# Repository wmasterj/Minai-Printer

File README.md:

# Minai Printer

A very cheap Wi-Fi receipt printer built for AI agents to print to.

The device is deliberately dumb: it receives a 384-pixel-wide black-and-white
image over Wi-Fi or USB and prints it on 58 mm thermal paper. Layout, fonts and
intelligence live in software upstream.

- Target build cost: about $26 per unit for the first 100, about $12 at 1,000 (estimates)
- Power: any USB-C charger, no battery
- Interface: one button, one light

## Documents

- [Hardware specification](docs/hardware-spec.md) — requirements, reference
  architecture, cost estimate, build plan, and what to ask a manufacturer for.

- [Reference design](hardware/README.md) — schematic, routed board, gerbers
  and parts list with links for the main circuit board.

- [Enclosure](hardware/enclosure/README.md) — 3D model of the case, with
  STEP and STL files for the four printed parts.

## Status

Specification and a first-pass reference board design, checked in software
only, plus a concept enclosure. Nothing has been built. No firmware yet.

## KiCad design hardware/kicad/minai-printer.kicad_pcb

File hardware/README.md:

# Minai Printer — main board reference design (rev 0.1)

A complete first-pass design of the printer's one circuit board: schematic,
routed 2-layer board, manufacturing files and parts list.

**Status: designed and rule-checked in software only. Nothing has been built
or powered. Treat it as a starting point for an electronics engineer or
supplier to review, not as files to order 100 boards from.** The list of
things that must be checked first is in [Before ordering](#before-ordering).

| Top copper and silkscreen | Bottom copper |
|---|---|
|  |  |

## What is here

| Path | What it is |
|---|---|
| `kicad/minai-printer.kicad_pro` | KiCad 9 project. Open this to view or edit the schematic and board |
| `outputs/schematic.pdf` | Schematic, one A3 page |
| `outputs/board-top.pdf`, `board-bottom.pdf` | Board layers as PDF |
| `outputs/gerbers.zip` | Gerber and drill files for a PCB fabricator |
| `outputs/pick-and-place.csv` | Part positions for an assembly house |
| `outputs/bom.csv`, [`outputs/bom.md`](outputs/bom.md) | Parts list with search links for every line |
| `outputs/erc-report.txt`, `drc-report.txt` | KiCad rule-check reports |
| `gen/design.py` | The design itself: every part, pin, net and position, in one file |
| `gen/build.sh` | Regenerates everything above from `design.py` |

## The board at a glance

| Item | Value |
|---|---|
| Size | 62 × 49 mm, 2 layers, 1.6 mm, four M2 mounting holes |
| Parts | 53 placed parts, 31 BOM lines, all on the top side |
| Power in | USB-C, 5 V |
| Brain | ESP32-C3-WROOM-02 module (Wi-Fi, Bluetooth LE, native USB) |
| Print head drive | Direct from the module: data, clock, latch, two strobe groups |
| Head power | 5 V through a soft-started MOSFET switch, 2 × 1000 µF reservoir |
| Paper feed | DRV8833 dual H-bridge, 1 A current limit per coil |
| Sensing | Head thermistor, paper-out sensor, head-rail voltage |
| User interface | One button (also the firmware-flash button), one RGB LED |
| Mechanism connector | 30-pin, 1.0 mm pitch FPC |

### Pin map (ESP32-C3)

| GPIO | Signal | Notes |
|---|---|---|
| 0 | TM_ADC | Head thermistor, 30 kΩ divider |
| 1 | PS_ADC | Paper sensor phototransistor |
| 2 | HEAD_LAT | Latch, idle high (also satisfies the boot strap) |
| 3 | VH_SENSE | Head rail ÷ 2.47 |
| 4 | HEAD_CLK | Shift clock |
| 5 | VH_EN | High = head power and motor driver on. Pulled low |
| 6 | HEAD_DI | Shift data |
| 7 | HEAD_STB_A | Strobes 1–3. Pulled low |
| 8 | LED_DIN | RGB LED data, pulled high (boot strap) |
| 9 | BTN | Button to ground, pulled high (boot strap) |
| 10 | HEAD_STB_B | Strobes 4–6. Pulled low |
| 18 / 19 | USB D− / D+ | Flashing and USB serial |
| 20 / 21 | MOT_PH_A / MOT_PH_B | Motor phases; an inverter makes the complements |

All 13 usable pins are taken. That is why the motor uses two pins plus a
dual inverter instead of four pins.

## What was checked, and how

- **Schematic rule check (ERC): 0 errors.** 2 warnings, both about library
  bookkeeping (a custom symbol for the mechanism connector), not the circuit.
- **Board rule check (DRC): 0 errors, 0 unconnected nets, 0 shorts.** 31
  warnings, all silkscreen text overlapping pads or other text (cosmetic).
- **Schematic and board agree:** KiCad's parity check reports 0 differences,
  and both files are generated from the same netlist in `design.py`.

Not checked by anything: whether the circuit actually works, whether the
mechanism pinout is right, thermal behaviour, radio performance, EMC.

## Before ordering

These are known gaps, most important first.

1. **Mechanism pinout is not confirmed.** Connector J2 follows the Fujitsu
   FTP-628MCL101 layout. I could not open the datasheet from this session;
   pins 1–20, 23–24 and 27–30 match fragments of it found by web search;
   pins 21, 22 (ground) and 25, 26 (head power) are from memory. The
   compatible mechanism you actually buy (PT486F or similar) must be checked
   pin by pin against its own datasheet.
2. **Strobe polarity is assumed active-high.** R7 and R8 pull the strobes low
   so the head is off during reset. If the head is active-low, those two
   resistors must go to 3.3 V instead, or the head will burn at power-up.
3. **Motor coil pairing is assumed** to be pins 27–28 and 29–30. If the coils
   are paired differently the motor will not turn; this needs a board change,
   not firmware.
4. **FPC connector.** Fujitsu specifies Molex 52610-3071. The board uses the
   footprint for Molex 200528-0300 (same pitch and pin count) because that is
   what the KiCad library has. Contact side (top or bottom) and pin-1 end must
   match how the mechanism's cable reaches the board in the enclosure.
5. **Power tracks are thin.** The board was auto-routed. 5 V and head-power
   tracks are 0.5 mm; for 2 A pulses they should be 1 mm or wider, or copper
   pours. An engineer should hand-route the power path and review the rest.
6. **Motor is energised whenever head power is on.** Firmware must turn VH_EN
   off between print jobs or the motor sits at up to 1 A per coil.
7. **5 V supply behaviour is calculated, not measured**: soft-start timing
   (R10, R11, C10), droop during heavy black printing, and behaviour on weak
   USB ports all need bench testing.
8. **Mechanical layout came first, enclosure second.** Board size and
   connector, button and LED positions were chosen for routing. The
   [enclosure](enclosure/README.md) was then drawn around them.
9. **Module lifecycle.** Confirm with the supplier which ESP32-C3-WROOM-02
   variant is current before buying.
10. **Silkscreen** labels overlap in places and need tidying.

## Parts and links

I could not open supplier sites from this session, so links are of two
kinds: pages that came up in web search (marked *found*), and search links
built from the part number (marked *search*), which open a results page.

### The print mechanism (not on the board)

| What | Link |
|---|---|
| Fujitsu FTP-628MCL101/103 datasheet, maker's site (*found*) | https://www.fcl-components.com/downloads/MICRO/fcai/thermal-printers/ftp-628mcl101_103-72.pdf |
| Same datasheet, Mouser copy (*found*) | https://www.mouser.com/datasheet/2/164/ftp_628mcl101_103-1713842.pdf |
| FTP-628MCL101#50 full specification (*found*) | https://www.printertec.com.br/arquivos_download/FTP-628MCL101_50.pdf |
| Compatible mechanism, TP628 series (*found*) | https://www.oposprinter.com/tp628-thermal-printer-mechanism-series-compatible-with-fujitsu-ftp-628mcl101-product/ |
| Compatible mechanism listing, Made-in-China (*found*) | https://xiamenjrp.en.made-in-china.com/product/qbQJYTDrVUls/China-FTP-628mcl101.html |
| PT486F-101 retail listing (*found*) | https://www.shreyanspos.com/products/pt486f-101-58mm-thermal-printer-mechanism |
| PT486F price listing, $3.90–4.50 (*found*) | https://china.org.ru/product/1600620307316 |
| Alibaba (*search*) | https://www.alibaba.com/trade/search?SearchText=PT486F+thermal+printer+mechanism |

Figures from those sources: 384 dots, 176 Ω per dot, head and motor
4.2–8.5 V, logic 3.3 V or 5 V, thermistor 30 kΩ at 25 °C.

### Main parts on the board

| Ref | Part | Maker page | Buy (*search*) |
|---|---|---|---|
| U1 | ESP32-C3-WROOM-02-N4 Wi-Fi/BLE module | [Espressif](https://www.espressif.com/en/products/modules/esp32-c3) | [LCSC](https://www.lcsc.com/search?q=ESP32-C3-WROOM-02-N4) · [DigiKey](https://www.digikey.com/en/products/result?keywords=ESP32-C3-WROOM-02-N4) |
| U3 | DRV8833PWR motor driver | [TI](https://www.ti.com/product/DRV8833) | [LCSC](https://www.lcsc.com/search?q=DRV8833PWR) · [DigiKey](https://www.digikey.com/en/products/result?keywords=DRV8833PWR) |
| U2 | AP2112K-3.3 regulator | [Diodes Inc.](https://www.diodes.com/part/view/AP2112) | [LCSC](https://www.lcsc.com/search?q=AP2112K-3.3TRG1) · [DigiKey](https://www.digikey.com/en/products/result?keywords=AP2112K-3.3TRG1) |
| U4 | 74LVC2G04 dual inverter | [Nexperia](https://www.nexperia.com/product/74LVC2G04GW) | [LCSC](https://www.lcsc.com/search?q=74LVC2G04GW) · [DigiKey](https://www.digikey.com/en/products/result?keywords=74LVC2G04GW) |
| U5 | USBLC6-2SC6 USB protection | [ST](https://www.st.com/en/protection-devices/usblc6-2.html) | [LCSC](https://www.lcsc.com/search?q=USBLC6-2SC6) · [DigiKey](https://www.digikey.com/en/products/result?keywords=USBLC6-2SC6) |
| Q1 | AO3401A P-channel MOSFET | | [LCSC](https://www.lcsc.com/search?q=AO3401A) · [DigiKey](https://www.digikey.com/en/products/result?keywords=AO3401A) |
| Q2 | 2N7002 N-channel MOSFET | | [LCSC](https://www.lcsc.com/search?q=2N7002) · [DigiKey](https://www.digikey.com/en/products/result?keywords=2N7002) |
| D2 | SK6812MINI RGB LED | | [LCSC](https://www.lcsc.com/search?q=SK6812MINI) · [DigiKey](https://www.digikey.com/en/products/result?keywords=SK6812MINI) |
| J1 | HRO TYPE-C-31-M-12 USB-C socket | | [LCSC](https://www.lcsc.com/search?q=TYPE-C-31-M-12) |
| J2 | Molex 200528-0300 FPC connector | | [LCSC](https://www.lcsc.com/search?q=200528-0300) · [DigiKey](https://www.digikey.com/en/products/result?keywords=2005280300) |

Every other line (resistors, capacitors, fuse, diode, switch) is in
[`outputs/bom.md`](outputs/bom.md) with the same kind of search links.

## Rebuilding

`gen/design.py` is the source. To change the circuit or move a part, edit it
and run:

```bash
FREEROUTING_JAR=/path/to/freerouting.jar hardware/gen/build.sh
```

Add `--route` to re-place and re-route the board. Routing is automatic and
gives a different result every run; some runs leave a net unrouted or
create a short, so check `outputs/drc-report.txt` each time. Editing the
board by hand in KiCad is fine too, but a later `--route` run will discard
those edits.

Requirements: Docker with the `kicad/kicad:9.0` image, Java 17 or newer, and
the Freerouting jar (tested with v2.0.1).

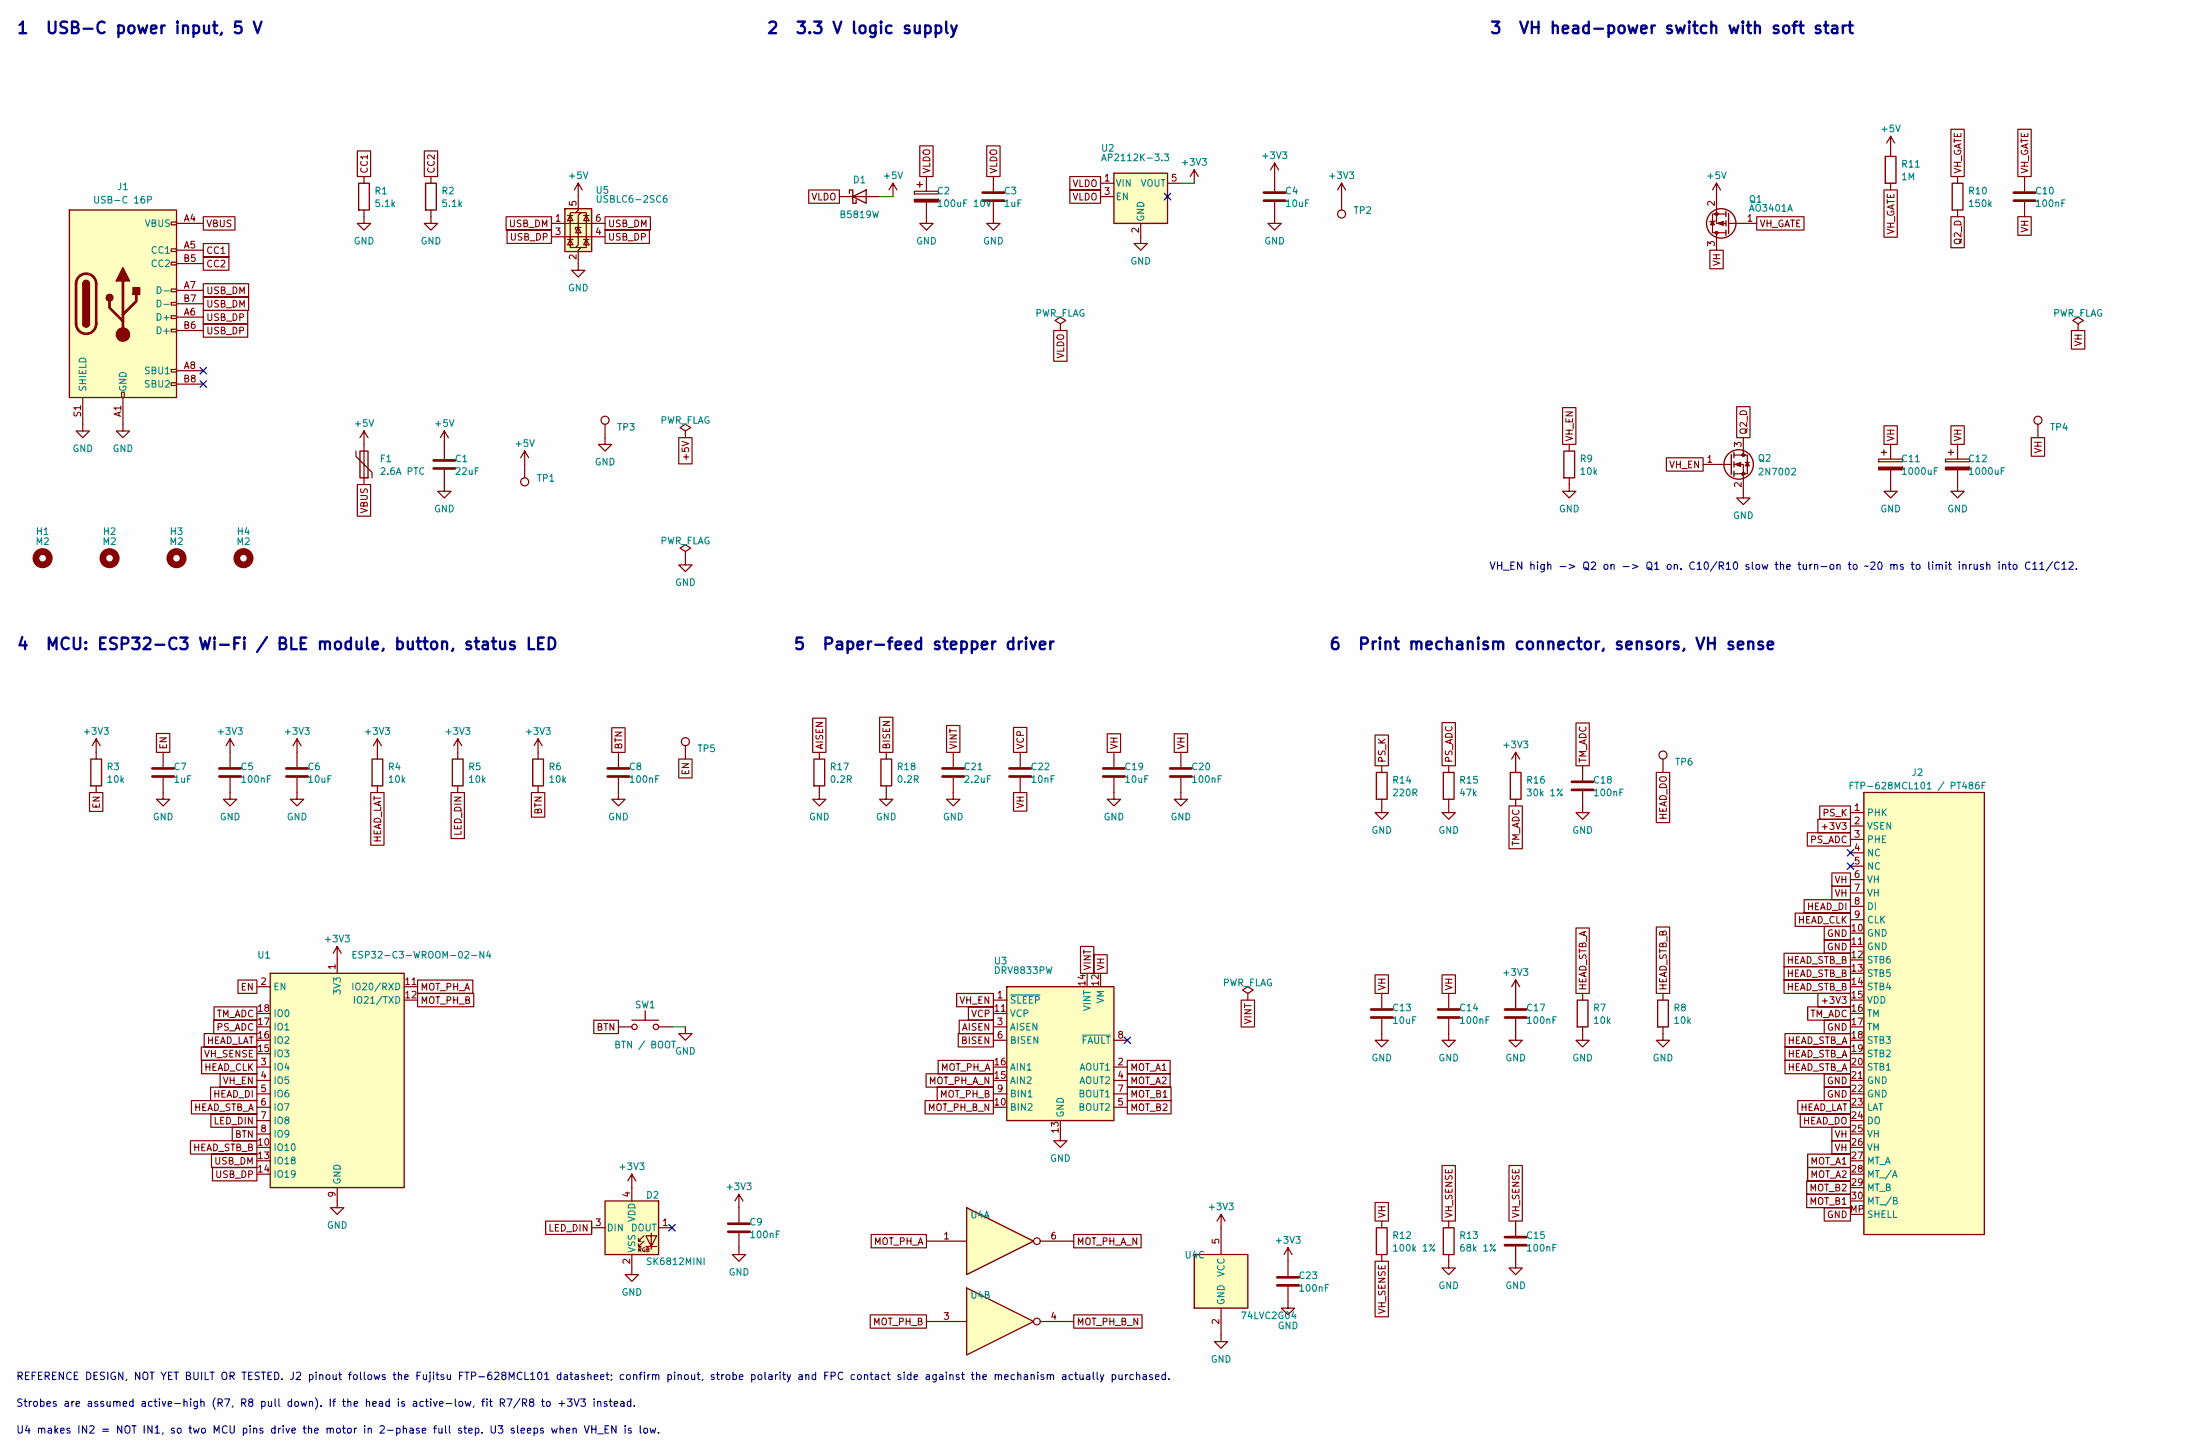
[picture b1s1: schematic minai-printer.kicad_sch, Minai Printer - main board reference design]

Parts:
C1: 22uF; C_0805_2012Metric
C2: 100uF 10V; CP_Elec_6.3x5.4
C3, C7: 1uF; C_0603_1608Metric
C4, C6, C13, C19: 10uF; C_0805_2012Metric
C5, C8, C9, C10, C14, C15, C17, C18, C20, C23: 100nF; C_0603_1608Metric
C11, C12: 1000uF; CP_Radial_D8.0mm_P3.50mm
C21: 2.2uF; C_0603_1608Metric
C22: 10nF; C_0603_1608Metric
D1: B5819W; D_SOD-123; MPN B5819W
D2: SK6812MINI; LED_SK6812MINI_PLCC4_3.5x3.5mm_P1.75mm; MPN SK6812MINI
F1: 2.6A PTC; Fuse_1812_4532Metric; MPN 1812L260/16
H1, H2, H3, H4: M2; MountingHole_2.2mm_M2
J1: USB-C 16P; USB_C_Receptacle_HRO_TYPE-C-31-M-12; MPN TYPE-C-31-M-12
J2: FTP-628MCL101 / PT486F; Molex_200528-0300_1x30-1MP_P1.00mm_Horizontal; MPN 200528-0300 (Fujitsu specifies Molex 52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
Q1: AO3401A; SOT-23; MPN AO3401A
Q2: 2N7002; SOT-23; MPN 2N7002
R1, R2: 5.1k; R_0603_1608Metric
R3, R4, R5, R6, R7, R8, R9: 10k; R_0603_1608Metric
R10: 150k; R_0603_1608Metric
R11: 1M; R_0603_1608Metric
R12: 100k 1%; R_0603_1608Metric
R13: 68k 1%; R_0603_1608Metric
R14: 220R; R_0603_1608Metric
R15: 47k; R_0603_1608Metric
R16: 30k 1%; R_0603_1608Metric
R17, R18: 0.2R; R_0805_2012Metric
SW1: BTN / BOOT; SW_PUSH_6mm; MPN TS-1187 / B3F class
TP1: +5V; TestPoint_Pad_D1.5mm
TP2: +3V3; TestPoint_Pad_D1.5mm
TP3: GND; TestPoint_Pad_D1.5mm
TP4: VH; TestPoint_Pad_D1.5mm
TP5: EN; TestPoint_Pad_D1.5mm
TP6: HEAD_DO; TestPoint_Pad_D1.5mm
U1: ESP32-C3-WROOM-02-N4; ESP32-C3-WROOM-02; MPN ESP32-C3-WROOM-02-N4
U2: AP2112K-3.3; SOT-23-5; MPN AP2112K-3.3TRG1
U3: DRV8833PW; TSSOP-16_4.4x5mm_P0.65mm; MPN DRV8833PWR
U4: 74LVC2G04; SOT-363_SC-70-6; MPN 74LVC2G04GW
U5: USBLC6-2SC6; SOT-23-6; MPN USBLC6-2SC6

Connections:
+3V3: C4.1, C5.1, C6.1, C9.1, C17.1, C23.1, D2.4 (VDD), J2.2 (VSEN), J2.15 (VDD), R3.1, R4.1, R5.1, R6.1, R16.1, TP2.1, U1.1 (3V3), U2.5 (VOUT), U4.5 (VCC)
+5V: C1.1, D1.2 (A), F1.2, Q1.2 (S), R11.1, TP1.1, U5.5 (VBUS)
AISEN: R17.1, U3.3 (AISEN)
BISEN: R18.1, U3.6 (BISEN)
BTN: C8.1, R6.2, SW1.1, U1.8 (IO9)
CC1: J1.A5 (CC1), R1.1
CC2: J1.B5 (CC2), R2.1
EN: C7.1, R3.2, TP5.1, U1.2 (EN)
GND: C1.2, C2.2, C3.2, C4.2, C5.2, C6.2, C7.2, C8.2, C9.2, C11.2, C12.2, C13.2, C14.2, C15.2, C17.2, C18.2, C19.2, C20.2, C21.2, C23.2, D2.2 (VSS), J1.A1 (GND), J1.A12 (GND), J1.B1 (GND), J1.B12 (GND), J1.S1 (SHIELD), J2.10 (GND), J2.11 (GND), J2.17 (TM), J2.21 (GND), J2.22 (GND), J2.MP (SHELL), Q2.2 (S), R1.2, R2.2, R7.2, R8.2, R9.2, R13.2, R14.2, R15.2, R17.2, R18.2, SW1.2, TP3.1, U1.9 (GND), U1.19 (GND), U2.2 (GND), U3.13 (GND), U4.2 (GND), U5.2 (GND)
HEAD_CLK: J2.9 (CLK), U1.3 (IO4)
HEAD_DI: J2.8 (DI), U1.5 (IO6)
HEAD_DO: J2.24 (DO), TP6.1
HEAD_LAT: J2.23 (LAT), R4.2, U1.16 (IO2)
HEAD_STB_A: J2.18 (STB3), J2.19 (STB2), J2.20 (STB1), R7.1, U1.6 (IO7)
HEAD_STB_B: J2.12 (STB6), J2.13 (STB5), J2.14 (STB4), R8.1, U1.10 (IO10)
LED_DIN: D2.3 (DIN), R5.2, U1.7 (IO8)
MOT_A1: J2.27 (MT_A), U3.2 (AOUT1)
MOT_A2: J2.28 (MT_/A), U3.4 (AOUT2)
MOT_B1: J2.30 (MT_/B), U3.7 (BOUT1)
MOT_B2: J2.29 (MT_B), U3.5 (BOUT2)
MOT_PH_A: U1.11 (IO20/RXD), U3.16 (AIN1), U4.1
MOT_PH_A_N: U3.15 (AIN2), U4.6
MOT_PH_B: U1.12 (IO21/TXD), U3.9 (BIN1), U4.3
MOT_PH_B_N: U3.10 (BIN2), U4.4
PS_ADC: J2.3 (PHE), R15.1, U1.17 (IO1)
PS_K: J2.1 (PHK), R14.1
Q2_D: Q2.3 (D), R10.2
TM_ADC: C18.1, J2.16 (TM), R16.2, U1.18 (IO0)
USB_DM: J1.A7 (D-), J1.B7 (D-), U1.13 (IO18), U5.1 (I/O1), U5.6 (I/O1)
USB_DP: J1.A6 (D+), J1.B6 (D+), U1.14 (IO19), U5.3 (I/O2), U5.4 (I/O2)
VBUS: F1.1, J1.A4 (VBUS), J1.A9 (VBUS), J1.B4 (VBUS), J1.B9 (VBUS)
VCP: C22.1, U3.11 (VCP)
VH: C10.2, C11.1, C12.1, C13.1, C14.1, C19.1, C20.1, C22.2, J2.6 (VH), J2.7 (VH), J2.25 (VH), J2.26 (VH), Q1.3 (D), R12.1, TP4.1, U3.12 (VM)
VH_EN: Q2.1 (G), R9.1, U1.4 (IO5), U3.1 (~SLEEP)
VH_GATE: C10.1, Q1.1 (G), R10.1, R11.2
VH_SENSE: C15.1, R12.2, R13.1, U1.15 (IO3)
VINT: C21.1, U3.14 (VINT)
VLDO: C2.1, C3.1, D1.1 (K), U2.1 (VIN), U2.3 (EN)

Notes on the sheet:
1 USB-C power input, 5 V
2 3.3 V logic supply
3 VH head-power switch with soft start
4 MCU: ESP32-C3 Wi-Fi / BLE module, button, status LED
5 Paper-feed stepper driver
6 Print mechanism connector, sensors, VH sense
REFERENCE DESIGN, NOT YET BUILT OR TESTED. J2 pinout follows the Fujitsu FTP-628MCL101 datasheet; confirm pinout, strobe polarity and FPC contact side against the mechanism actually purchased.
Strobes are assumed active-high (R7, R8 pull down). If the head is active-low, fit R7/R8 to +3V3 instead.
VH_EN high -> Q2 on -> Q1 on. C10/R10 slow the turn-on to ~20 ms to limit inrush into C11/C12.
U4 makes IN2 = NOT IN1, so two MCU pins drive the motor in 2-phase full step. U3 sleeps when VH_EN is low.

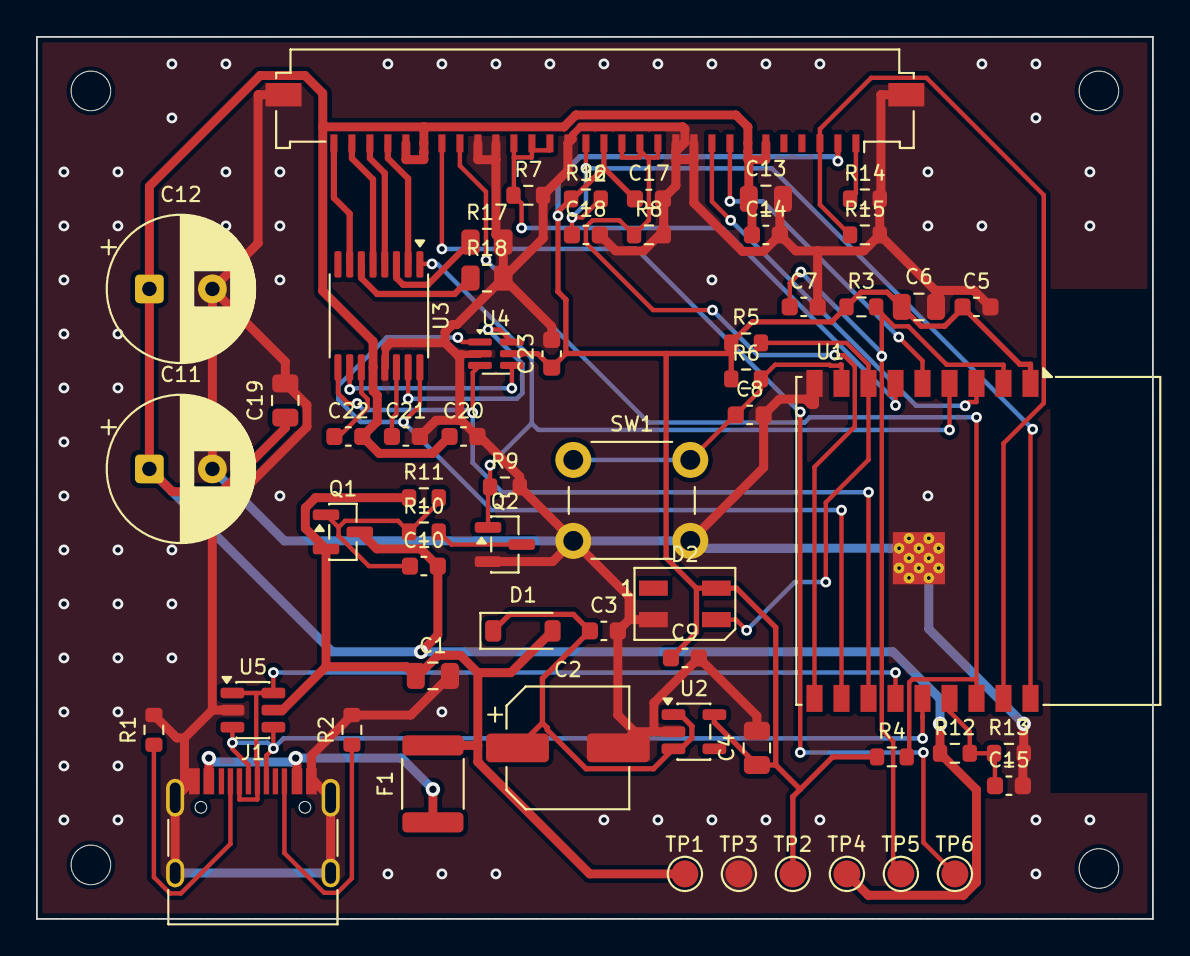
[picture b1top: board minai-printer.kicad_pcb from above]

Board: 2 copper layers, 62.0 x 49.0 mm, 63 parts (0 on the bottom side), 38 nets.

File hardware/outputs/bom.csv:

Designators,Qty,Value,Description,Footprint,Manufacturer,Part number,LCSC search,DigiKey search,Manufacturer page
C1,1,22uF,Capacitor 22uF 10V X5R 0805,C_0805_2012Metric,,,https://www.lcsc.com/search?q=22uF%200805%20capacitor,https://www.digikey.com/en/products/result?keywords=22uF%200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,
C2,1,100uF 10V,"Aluminium electrolytic 100uF 10V, 6.3x5.4 mm SMD",CP_Elec_6.3x5.4,,,https://www.lcsc.com/search?q=100uF%2010V%20Elec%20capacitor,https://www.digikey.com/en/products/result?keywords=100uF%20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,
C3 C7,2,1uF,Capacitor 1uF 16V X7R 0603,C_0603_1608Metric,,,https://www.lcsc.com/search?q=1uF%200603%20capacitor,https://www.digikey.com/en/products/result?keywords=1uF%2006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,
C4 C6 C13 C19,4,10uF,Capacitor 10uF 10V X5R 0805,C_0805_2012Metric,,,https://www.lcsc.com/search?q=10uF%200805%20capacitor,https://www.digikey.com/en/products/result?keywords=10uF%200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,
C5 C8 C9 C10 C14 C15 C17 C18 C20 C23,10,100nF,Capacitor 100nF 16V X7R 0603,C_0603_1608Metric,,,https://www.lcsc.com/search?q=100nF%200603%20capacitor,https://www.digikey.com/en/products/result?keywords=100nF%20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,
C11 C12,2,1000uF,"Aluminium electrolytic 1000uF 10V low-ESR, 8 mm dia, 3.5 mm pitch",CP_Radial_D8.0mm_P3.50mm,,,https://www.lcsc.com/search?q=1000uF%20Radial%20capacitor,https://www.digikey.com/en/products/result?keywords=1000uF%2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,
C21,1,2.2uF,Capacitor 2.2uF 16V X7R 0603,C_0603_1608Metric,,,https://www.lcsc.com/search?q=2.2uF%200603%20capacitor,https://www.digikey.com/en/products/result?keywords=2.2uF%20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,
C22,1,10nF,Capacitor 10nF 16V X7R (charge pump),C_0603_1608Metric,,,https://www.lcsc.com/search?q=10nF%200603%20capacitor,https://www.digikey.com/en/products/result?keywords=10nF%200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,
D1,1,B5819W,Schottky diode 40V 1A SOD-123,D_SOD-123,generic,B5819W,https://www.lcsc.com/search?q=B5819W,https://www.digikey.com/en/products/result?keywords=B5819W,
D2,1,SK6812MINI,Addressable RGB LED 3535,LED_SK6812MINI_PLCC4_3.5x3.5mm_P1.75mm,Opsco / Worldsemi,SK6812MINI,https://www.lcsc.com/search?q=SK6812MINI,https://www.digikey.com/en/products/result?keywords=SK6812MINI,
F1,1,2.6A PTC,"Resettable fuse, 2.6 A hold, 1812",Fuse_1812_4532Metric,Littelfuse (or equivalent),1812L260/16,https://www.lcsc.com/search?q=1812L260,https://www.digikey.com/en/products/result?keywords=1812L260,
J1,1,USB-C 16P,"USB Type-C receptacle, 16 pin, USB 2.0, SMT",USB_C_Receptacle_HRO_TYPE-C-31-M-12,Korean Hroparts (HRO),TYPE-C-31-M-12,https://www.lcsc.com/search?q=TYPE-C-31-M-12,https://www.digikey.com/en/products/result?keywords=TYPE-C-31-M-12,
J2,1,FTP-628MCL101 / PT486F,"FFC/FPC connector 30 pos 1.0 mm pitch, right angle ZIF",Molex_200528-0300_1x30-1MP_P1.00mm_Horizontal,Molex,200528-0300 (Fujitsu specifies Molex 52610-3071),https://www.lcsc.com/search?q=200528-0300,https://www.digikey.com/en/products/result?keywords=200528-0300,
Q1,1,AO3401A,"P-channel MOSFET 30V 4A, VH high-side switch",SOT-23,Alpha & Omega,AO3401A,https://www.lcsc.com/search?q=AO3401A,https://www.digikey.com/en/products/result?keywords=AO3401A,
Q2,1,2N7002,"N-channel MOSFET 60V, level shifter",SOT-23,generic,2N7002,https://www.lcsc.com/search?q=2N7002,https://www.digikey.com/en/products/result?keywords=2N7002,
R1 R2,2,5.1k,Resistor 5.1k 0603,R_0603_1608Metric,,,https://www.lcsc.com/search?q=5.1k%200603%20resistor,https://www.digikey.com/en/products/result?keywords=5.1k%200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,
R3 R4 R5 R6 R7 R8 R9,7,10k,Resistor 10k 0603,R_0603_1608Metric,,,https://www.lcsc.com/search?q=10k%200603%20resistor,https://www.digikey.com/en/products/result?keywords=10k%2006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,
R10,1,150k,Resistor 150k 0603,R_0603_1608Metric,,,https://www.lcsc.com/search?q=150k%200603%20resistor,https://www.digikey.com/en/products/result?keywords=150k%200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,
R11,1,1M,Resistor 1M 0603,R_0603_1608Metric,,,https://www.lcsc.com/search?q=1M%200603%20resistor,https://www.digikey.com/en/products/result?keywords=1M%20060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,
R12,1,100k 1%,Resistor 100k 1% 0603,R_0603_1608Metric,,,https://www.lcsc.com/search?q=100k%200603%20resistor,https://www.digikey.com/en/products/result?keywords=100k%200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,
R13,1,68k 1%,Resistor 68k 1% 0603,R_0603_1608Metric,,,https://www.lcsc.com/search?q=68k%200603%20resistor,https://www.digikey.com/en/products/result?keywords=68k%2006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,
R14,1,220R,Resistor 220R (paper sensor LED current),R_0603_1608Metric,,,https://www.lcsc.com/search?q=220R%200603%20resistor,https://www.digikey.com/en/products/result?keywords=220R%200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,
R15,1,47k,Resistor 47k (paper sensor load),R_0603_1608Metric,,,https://www.lcsc.com/search?q=47k%200603%20resistor,https://www.digikey.com/en/products/result?keywords=47k%2006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,
R16,1,30k 1%,Resistor 30k 1% (thermistor divider),R_0603_1608Metric,,,https://www.lcsc.com/search?q=30k%200603%20resistor,https://www.digikey.com/en/products/result?keywords=30k%2006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,
R17 R18,2,0.2R,Current-sense resistor 0.2 ohm 1% 0805 (1 A limit),R_0805_2012Metric,,,https://www.lcsc.com/search?q=0.2R%200805%20resistor,https://www.digikey.com/en/products/result?keywords=0.2R%200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,
SW1,1,BTN / BOOT,Tactile switch 6x6 mm through-hole; actuator height to suit keycap,SW_PUSH_6mm,generic,TS-1187 / B3F class,https://www.lcsc.com/search?q=TS-1187,https://www.digikey.com/en/products/result?keywords=TS-1187,
U1,1,ESP32-C3-WROOM-02-N4,"Wi-Fi + Bluetooth LE module, RISC-V, 4 MB flash, PCB antenna",ESP32-C3-WROOM-02,Espressif,ESP32-C3-WROOM-02-N4,https://www.lcsc.com/search?q=ESP32-C3-WROOM-02-N4,https://www.digikey.com/en/products/result?keywords=ESP32-C3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,https://www.espressif.com/en/products/modules/esp32-c3
U2,1,AP2112K-3.3,3.3 V 600 mA low-dropout regulator,SOT-23-5,Diodes Inc.,AP2112K-3.3TRG1,https://www.lcsc.com/search?q=AP2112K-3.3TRG1,https://www.digikey.com/en/products/result?keywords=AP2112K-3.3TRG1,https://www.diodes.com/part/view/AP2112
U3,1,DRV8833PW,"Dual H-bridge motor driver, 1.5 A, TSSOP-16",TSSOP-16_4.4x5mm_P0.65mm,Texas Instruments (or pin-compatible),DRV8833PWR,https://www.lcsc.com/search?q=DRV8833PWR,https://www.digikey.com/en/products/result?keywords=DRV8833PWR,https://www.ti.com/product/DRV8833
U4,1,74LVC2G04,"Dual inverter, generates complementary motor phase signals",SOT-363_SC-70-6,Nexperia (or equivalent),74LVC2G04GW,https://www.lcsc.com/search?q=74LVC2G04GW,https://www.digikey.com/en/products/result?keywords=74LVC2G04GW,https://www.nexperia.com/product/74LVC2G04GW
U5,1,USBLC6-2SC6,USB ESD protection diode array,SOT-23-6,STMicroelectronics,USBLC6-2SC6,https://www.lcsc.com/search?q=USBLC6-2SC6,https://www.digikey.com/en/products/result?keywords=USBLC6-2SC6,https://www.st.com/en/protection-devices/usblc6-2.html

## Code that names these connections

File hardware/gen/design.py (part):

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  {"1": "+3V3", "9": "GND", "19": "GND", "2": "EN",
   "18": "TM_ADC",       # IO0  ADC1_CH0  head thermistor
   "17": "PS_ADC",       # IO1  ADC1_CH1  paper sensor
   "16": "HEAD_LAT",     # IO2  strapping, pulled up
   "15": "VH_SENSE",     # IO3  ADC1_CH3  head rail voltage
   "3": "HEAD_CLK",      # IO4
   "4": "VH_EN",         # IO5
   "5": "HEAD_DI",       # IO6
   "6": "HEAD_STB_A",    # IO7
   "7": "LED_DIN",       # IO8  strapping, pulled up
   "8": "BTN",           # IO9  strapping / boot button
   "10": "HEAD_STB_B",   # IO10
   "13": "USB_DM",       # IO18
   "14": "USB_DP",       # IO19
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               "confirm pinout, strobe polarity and FPC contact side against the mechanism actually purchased."),
    ((6, 110.5), "Strobes are assumed active-high (R7, R8 pull down). If the head is active-low, fit R7/R8 to +3V3 instead."),
    ((116, 48), "VH_EN high -> Q2 on -> Q1 on. C10/R10 slow the turn-on to ~20 ms to limit inrush into C11/C12."),
    ((6, 112.5), "U4 makes IN2 = NOT IN1, so two MCU pins drive the motor in 2-phase full step. U3 sleeps when VH_EN is low."),
]

# ------------------------------------------------------------ board placement
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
